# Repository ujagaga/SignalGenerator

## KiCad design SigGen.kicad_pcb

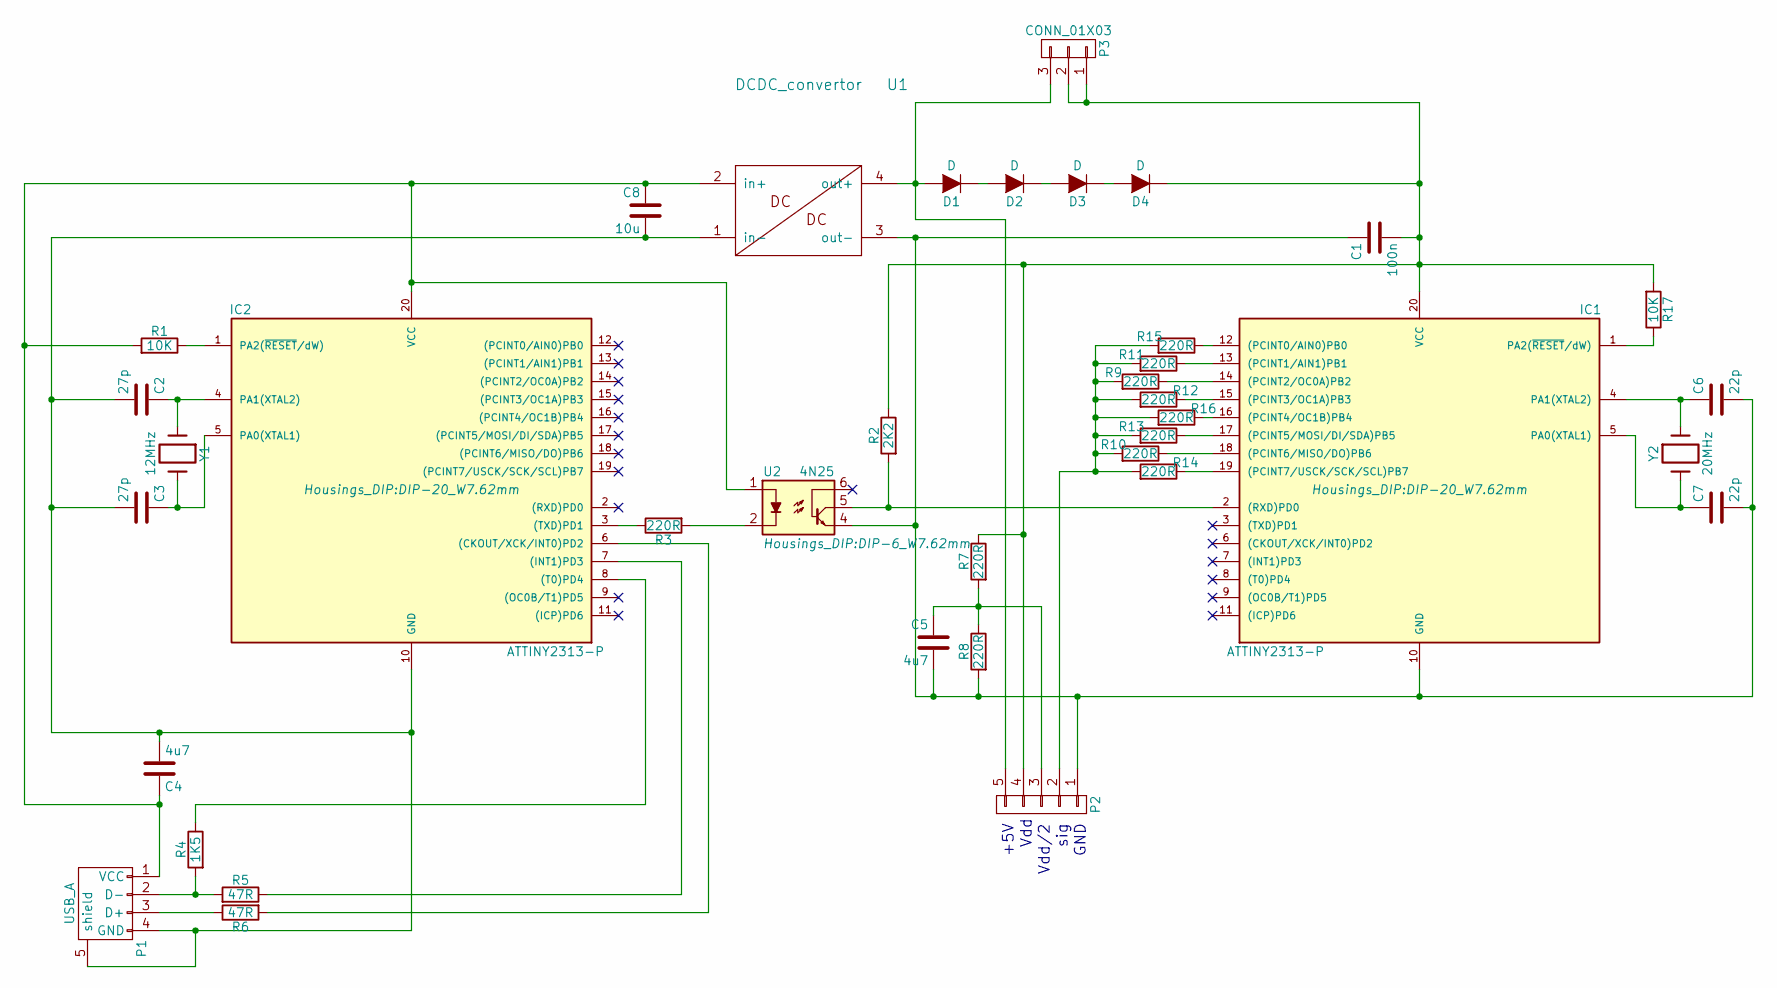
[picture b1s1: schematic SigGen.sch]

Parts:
C1: 100n; C_0805_HandSoldering
C2, C3: 27p; C_0805_HandSoldering
C4, C5: 4u7; C_0805_HandSoldering
C6, C7: 22p; C_0805_HandSoldering
C8: 10u; C_0805_HandSoldering
D1, D2, D3, D4: D; C_0805_HandSoldering
IC1, IC2: ATTINY2313-P; DIP-20_W7.62mm
P1: USB_A
P2: CONN_01X05; Socket_Strip_Straight_1x05
P3: CONN_01X03; Socket_Strip_Straight_1x03
R1, R17: 10K; R_0805_HandSoldering
R2: 2K2; R_0805_HandSoldering
R3, R7, R8, R9, R10, R11, R12, R13, R14, R15, R16: 220R; R_0805_HandSoldering
R4: 1K5; R_0805_HandSoldering
R5, R6: 47R; R_0805_HandSoldering
U1: DCDC_convertor; Socket_Strip_Straight_1x04
U2: 4N25; DIP-6_W7.62mm
Y1: 12MHz; Crystal_HC49-U_Vertical
Y2: 20MHz; Crystal_HC49-U_Vertical

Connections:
unnamed: C1.1, C5.2, C6.2, C7.2, IC1.10 (GND), P2.1, R8.2, U1.3 (out-), U2.4
unnamed: C1.2, D4.1 (K), IC1.20 (VCC), P2.4, P3.1, P3.2, R2.1, R7.1, R17.2
unnamed: C2.1, IC2.4 (PA1(XTAL2)), Y1.1
unnamed: C2.2, C3.2, C4.2, C8.2, IC2.10 (GND), P1.4 (GND), P1.5 (shield), U1.1 (in-)
unnamed: C3.1, IC2.5 (PA0(XTAL1)), Y1.2
unnamed: C4.1, C8.1, IC2.20 (VCC), P1.1 (VCC), R1.2, U1.2 (in+), U2.1
unnamed: C5.1, P2.3, R7.2, R8.1
unnamed: C6.1, IC1.4 (PA1(XTAL2)), Y2.1
unnamed: C7.1, IC1.5 (PA0(XTAL1)), Y2.2
unnamed: D1.1 (K), D2.2 (A)
unnamed: D1.2 (A), P2.5, P3.3, U1.4 (out+)
unnamed: D2.1 (K), D3.2 (A)
unnamed: D3.1 (K), D4.2 (A)
unnamed: IC1.1 (PA2(~RESET~/dW)), R17.1
unnamed: IC1.2 ((RXD)PD0), R2.2, U2.5
unnamed: IC1.12 ((PCINT0/AIN0)PB0), R15.1
unnamed: IC1.13 ((PCINT1/AIN1)PB1), R11.1
unnamed: IC1.14 ((PCINT2/OC0A)PB2), R9.1
unnamed: IC1.15 ((PCINT3/OC1A)PB3), R12.1
unnamed: IC1.16 ((PCINT4/OC1B)PB4), R16.1
unnamed: IC1.17 ((PCINT5/MOSI/DI/SDA)PB5), R13.1
unnamed: IC1.18 ((PCINT6/MISO/DO)PB6), R10.1
unnamed: IC1.19 ((PCINT7/USCK/SCK/SCL)PB7), R14.1
unnamed: IC2.1 (PA2(~RESET~/dW)), R1.1
unnamed: IC2.3 ((TXD)PD1), R3.1
unnamed: IC2.6 ((CKOUT/XCK/INT0)PD2), R6.2
unnamed: IC2.7 ((INT1)PD3), R5.1
unnamed: IC2.8 ((T0)PD4), R4.1
unnamed: P1.2 (D-), R4.2, R5.2
unnamed: P1.3 (D+), R6.1
unnamed: P2.2, R9.2, R10.2, R11.2, R12.2, R13.2, R14.2, R15.2, R16.2
unnamed: R3.2, U2.2

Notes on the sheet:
+5V
Vdd
Vdd/2
sig
GND

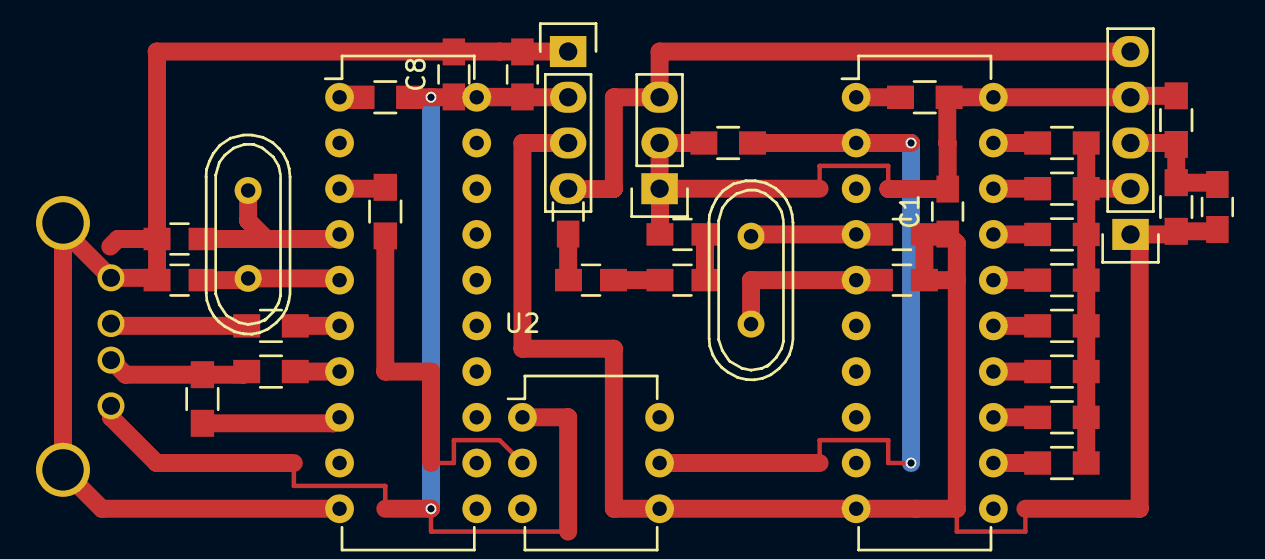
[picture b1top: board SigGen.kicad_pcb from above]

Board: 2 copper layers, 38 parts (1 on the bottom side), 32 nets.

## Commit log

2016-11-21 Updated schematic
2016-11-24 Updating PCB
2016-11-24 Finished the PCB
2016-11-25 Added USB device guide
2016-11-28 Working CDC
2016-11-28 Corrected the FW
2016-11-29 Completed CDC fw
2016-11-30 Finally working CDC as intended
2016-11-30 Working generator with 10ms minimum time
2016-12-01 Working on faster counting
2016-12-05 Faster counting completed
2016-12-28 Updated documentatuin
2016-12-29 Updated doc
